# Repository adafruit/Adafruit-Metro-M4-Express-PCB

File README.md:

## Adafruit Metro M4 Express PCB

<a href="http://www.adafruit.com/products/3382"><br/>
Click here to purchase one from the Adafruit shop</a>

PCB files for the Adafruit Metro Express M4. PCB format is EagleCAD schematic and board layout

For more details, check out the product pages at
* https://www.adafruit.com/products/3382

### Description

Are you ready? Really ready? Cause here comes the fastest, most powerful Metro ever. The Adafruit Metro M4 featuring the Microchip ATSAMD51. This Metro is like a bullet train, with it's 120MHz Cortex M4 with floating point support. Your code will zig and zag and zoom, and with a bunch of extra peripherals for support, this will for sure be your favorite new chipset.

To start off our ATSAMD51 journey we decided to kick it off with the classic 'Arduino compatible' shape and pinout you know and love. This Metro is the same size as the others, and is compatible with all our shields. It's got analog pins where you expect, and SPI/UART/I2C hardware support in the same spot as the Metro 328 and M0. But! It's powered with an ATSAMD51J19.

### License

Adafruit invests time and resources providing this open source design, please support Adafruit and open-source hardware by purchasing products from [Adafruit](https://www.adafruit.com)!

Designed by Limor Fried/Ladyada for Adafruit Industries.

Creative Commons Attribution/Share-Alike, all text above must be included in any redistribution. See license.txt for additional details.

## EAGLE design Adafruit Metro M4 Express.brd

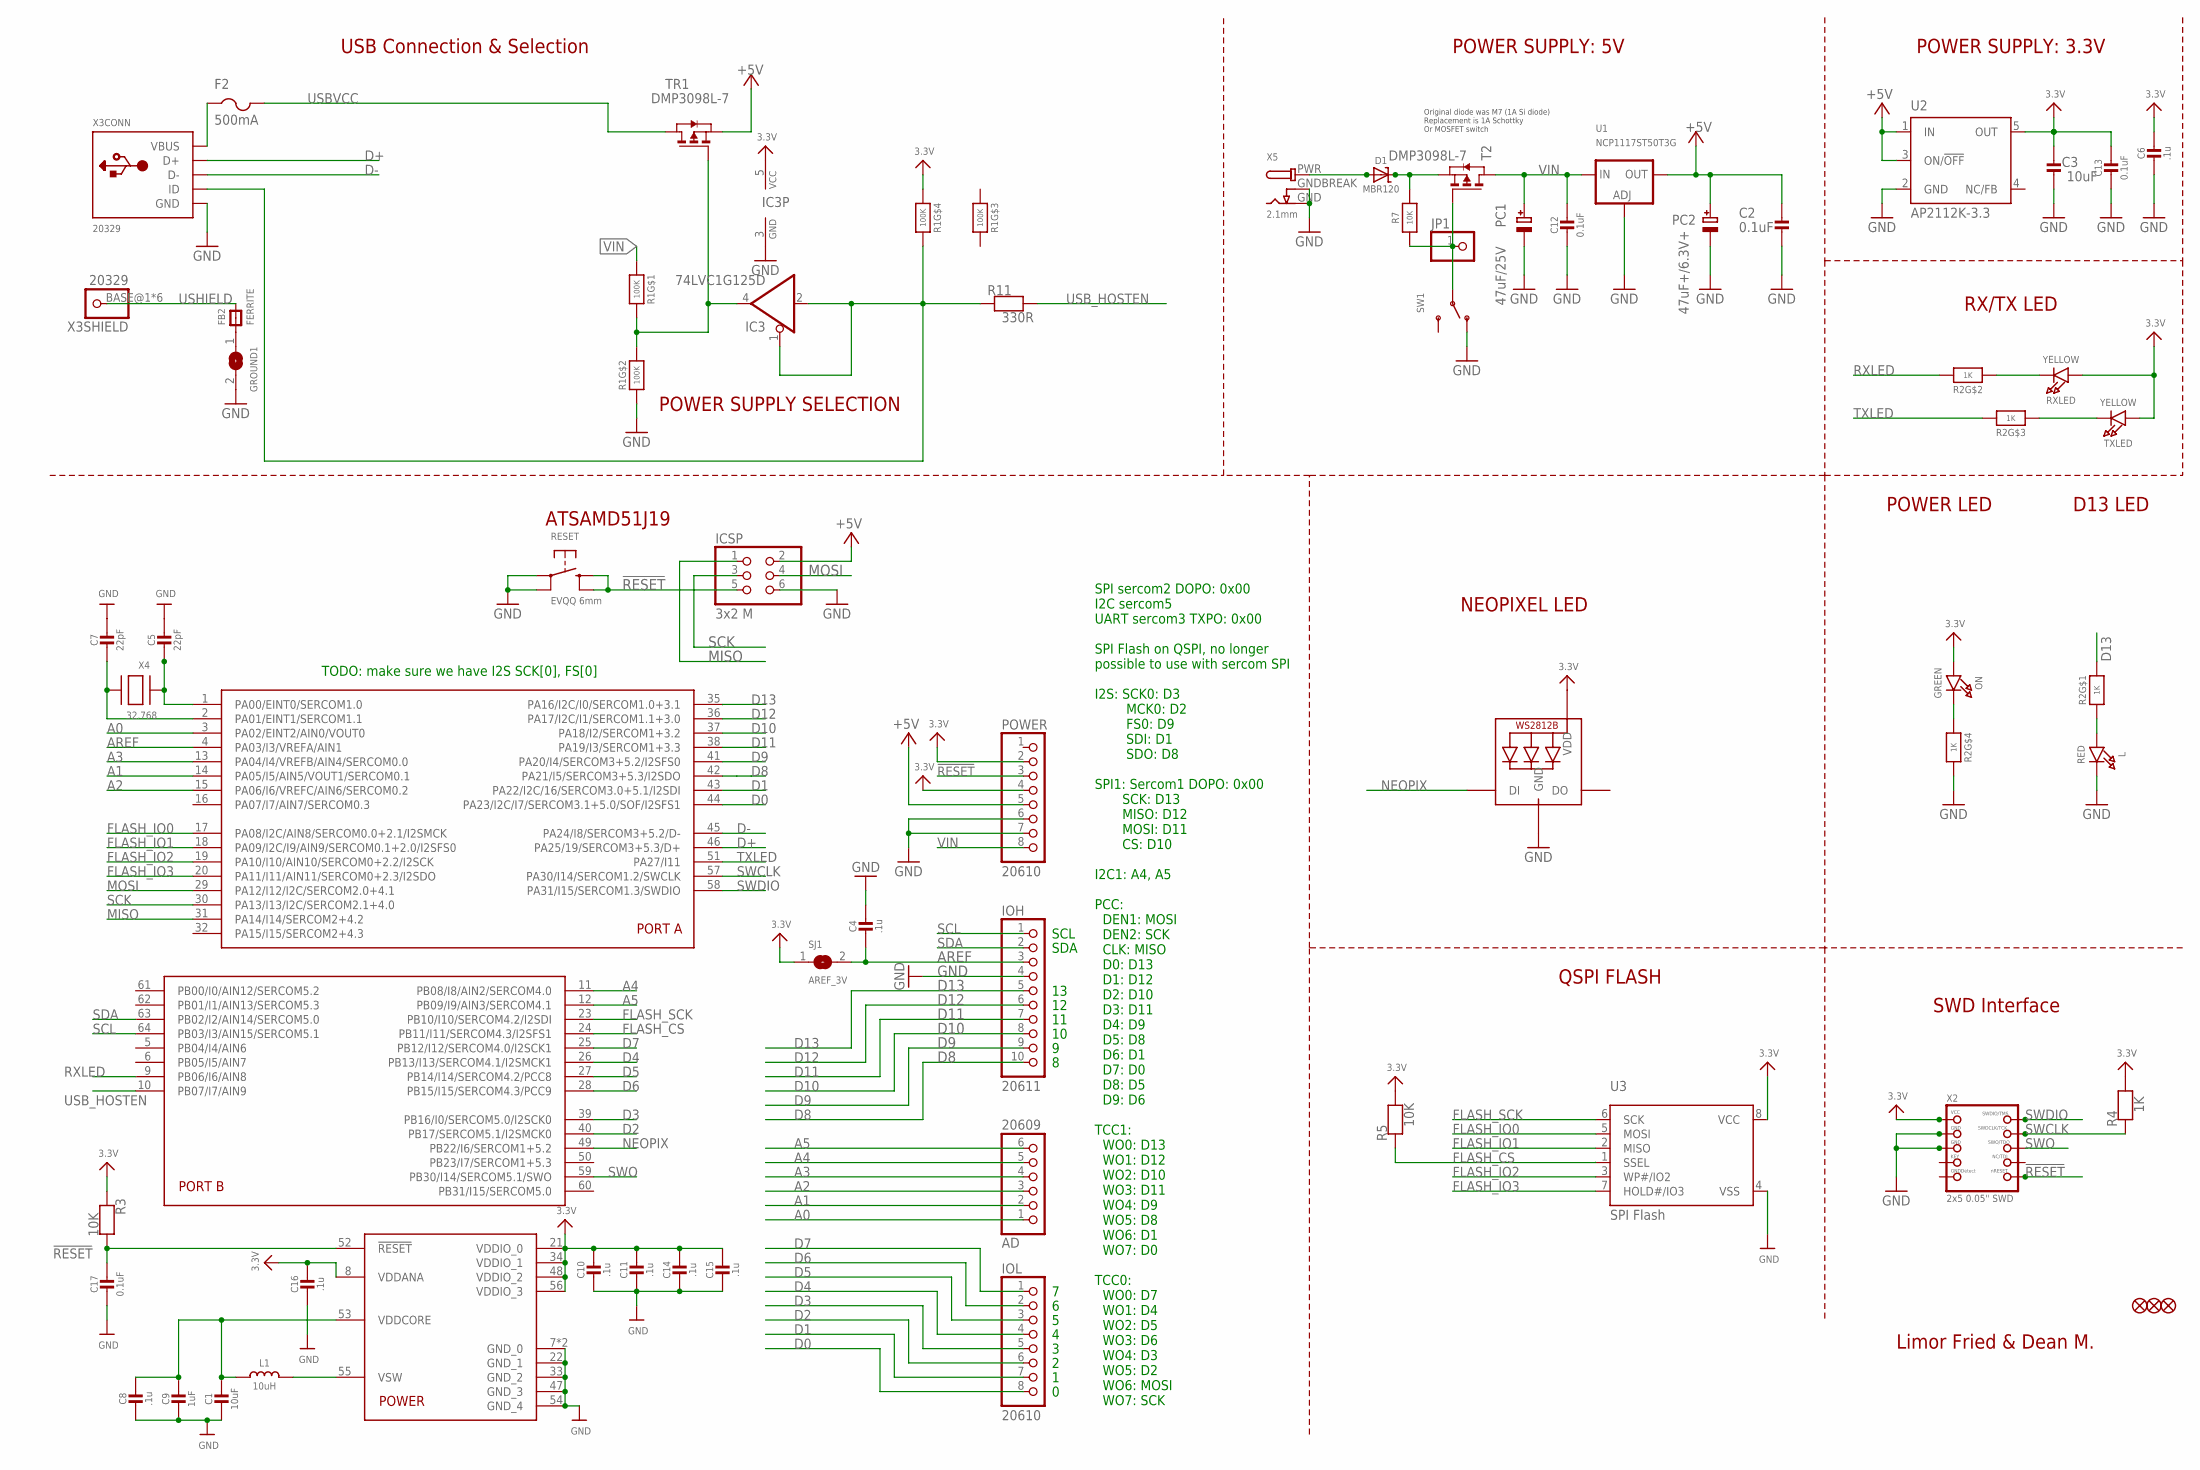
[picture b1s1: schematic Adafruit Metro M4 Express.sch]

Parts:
AD: 20609; 1X06_OVALWAVE
C1, C3: 10uF; 0805-NO
C2: 0.1uF; 0805-NO
C4, C6, C8, C10, C11, C14, C15, C16: .1u; 0603-NO
C5, C7: 22pF; 0603-NO
C9: 1uF; 0603-NO
C12, C13, C17: 0.1uF; 0603-NO
D1: MBR120; SOD-123
F2: 500mA; R1206
FB2: FERRITE; 0805-NO
FD1, FD2, FD3: FIDUCIAL_1MM
GROUND1: SOLDERJUMPERCLOSED; SOLDERJUMPER_CLOSEDWIRE
IC3: 74LVC1G125D; SOT23-5
ICSP: 3x2 M; 2X03_ROUND_70MIL
IOH: 20611; 1X10_OVALWAVE
IOL: 20610; 1X08_OVALWAVE
JP1: HEADER-1X1ROUND; 1X01_ROUND
L: RED; CHIPLED_0805_NOOUTLINE
L1: 10uH; INDUCTOR_1007
LED1: WS2812B3535; LED3535
ON: GREEN; CHIPLED_0805_NOOUTLINE
PC1: 47uF/25V; PANASONIC_D
PC2: 47uF+/6.3V+; PANASONIC_D
POWER: 20610; 1X08_OVALWAVE
R1: 100K; RESPACK_4X0603
R2: 1K; RESPACK_4X0603
R3, R5, R7: 10K; 0603-NO
R4: 1K; 0603-NO
R11: 330R; 0603-NO
RESET: EVQQ 6mm; EVQ-Q2
RXLED: YELLOW; CHIPLED_0805_NOOUTLINE
SJ1: AREF_3V; SOLDERJUMPER_CLOSEDWIRE
SW1: SWITCH_SPDT; SPDT_SMT_SSSS811101
T2: DMP3098L-7; SOT-23
TR1: DMP3098L-7; SOT-23
TXLED: YELLOW; CHIPLED_0805_NOOUTLINE
U1: NCP1117ST50T3G; SOT223-R
U2: AP2112K-3.3; SOT23-DBV
U3: SPI Flash; SOIC8_208MIL
U$1: ATSAMD51J; PQFN64-1
X2: 2x5 0.05" SWD; 2X05_1.27MM_BOX_POSTS
X3: 20329; 4UCONN_20329_V2
X4: 32.768; XTAL3215
X5: 2.1mm; DCJACK_2MM_PTH

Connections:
3.3V: C3.2, C6.2, C10.2, C11.2, C13.1, C14.2, C15.2, C16.2, IC3.5 (VCC), LED1.2 (VDD), ON.A, POWER.2, POWER.4, R1.4 (1), R3.1, R4.2, R5.2, RXLED.A, SJ1.1, TXLED.A, U2.5 (OUT), U3.8 (VCC), U$1.8 (VDDANA), U$1.21 (VDDIO_0), U$1.34 (VDDIO_1), U$1.48 (VDDIO_2), U$1.56 (VDDIO_3), X2.1 (VCC)
!RESET: C17.2, ICSP.5, POWER.3, R3.2, RESET.B (S), RESET.B' (S1), U$1.52 (!RESET), X2.10 (NRESET)
+5V: C2.2, ICSP.2, PC2.+, POWER.5, TR1.2 (S), U1.2 (OUT), U1.4 (OUT), U2.1 (IN), U2.3 (ON/!OFF)
A0: AD.1, U$1.3 (PA02/EINT2/AIN0/VOUT0)
A1: AD.2, U$1.14 (PA05/I5/AIN5/VOUT1/SERCOM0.1)
A2: AD.3, U$1.15 (PA06/I6/VREFC/AIN6/SERCOM0.2)
A3: AD.4, U$1.13 (PA04/I4/VREFB/AIN4/SERCOM0.0)
A4: AD.5, U$1.11 (PB08/I8/AIN2/SERCOM4.0)
A5: AD.6, U$1.12 (PB09/I9/AIN3/SERCOM4.1)
AREF: C4.1, IOH.3, SJ1.2, U$1.4 (PA03/I3/VREFA/AIN1)
D0: IOL.8, U$1.44 (PA23/I2C/I7/SERCOM3.1+5.0/SOF/I2SFS1)
D1: IOL.7, U$1.43 (PA22/I2C/16/SERCOM3.0+5.1/I2SDI)
D2: IOL.6, U$1.40 (PB17/SERCOM5.1/I2SMCK0)
D3: IOL.5, U$1.39 (PB16/I0/SERCOM5.0/I2SCK0)
D4: IOL.4, U$1.26 (PB13/I13/SERCOM4.1/I2SMCK1)
D5: IOL.3, U$1.27 (PB14/I14/SERCOM4.2/PCC8)
D6: IOL.2, U$1.28 (PB15/I15/SERCOM4.3/PCC9)
D7: IOL.1, U$1.25 (PB12/I12/SERCOM4.0/I2SCK1)
D8: IOH.10, U$1.42 (PA21/I5/SERCOM3+5.3/I2SDO)
D9: IOH.9, U$1.41 (PA20/I4/SERCOM3+5.2/I2SFS0)
D10: IOH.8, U$1.37 (PA18/I2/SERCOM1+3.2)
D11: IOH.7, U$1.38 (PA19/I3/SERCOM1+3.3)
D12: IOH.6, U$1.36 (PA17/I2C/I1/SERCOM1.1+3.0)
D13: IOH.5, R2.8 (2), U$1.35 (PA16/I2C/I0/SERCOM1.0+3.1)
D+: U$1.46 (PA25/19/SERCOM3+5.3/D+), X3.D+
D-: U$1.45 (PA24/I8/SERCOM3+5.2/D-), X3.D-
FLASH_CS: R5.1, U3.1 (SSEL), U$1.24 (PB11/I11/SERCOM4.3/I2SFS1)
FLASH_IO0: U3.5 (MOSI), U$1.17 (PA08/I2C/AIN8/SERCOM0.0+2.1/I2SMCK)
FLASH_IO1: U3.2 (MISO), U$1.18 (PA09/I2C/I9/AIN9/SERCOM0.1+2.0/I2SFS0)
FLASH_IO2: U3.3 (WP#/IO2), U$1.19 (PA10/I10/AIN10/SERCOM0+2.2/I2SCK)
FLASH_IO3: U3.7 (HOLD#/IO3), U$1.20 (PA11/I11/AIN11/SERCOM0+2.3/I2SDO)
FLASH_SCK: U3.6 (SCK), U$1.23 (PB10/I10/SERCOM4.2/I2SDI)
GND: C1.2, C2.1, C3.1, C4.2, C5.2, C6.1, C7.2, C8.1, C9.2, C10.1, C11.1, C12.2, C13.2, C14.1, C15.1, C16.1, C17.1, GROUND1.2, IC3.3 (GND), ICSP.6, IOH.4, L.C, LED1.4 (GND), PC1.-, PC2.-, POWER.6, POWER.7, R1.2 (1), R2.5 (2), RESET.A, RESET.A' (P1), SW1.A (O), U1.1 (ADJ), U2.2 (GND), U3.4 (VSS), U$1.7 (GND_0), U$1.22 (GND_1), U$1.33 (GND_2), U$1.47 (GND_3), U$1.54 (GND_4), U$1.EXP (GND_0), X2.3 (GND), X2.5 (GND), X3.GND, X5.GND, X5.GNDBREAK
MISO: ICSP.1, U$1.31 (PA14/I14/SERCOM2+4.2)
MOSI: ICSP.4, U$1.29 (PA12/I12/I2C/SERCOM2.0+4.1)
unnamed: L.A, R2.1
unnamed: FB2.1, GROUND1.1
unnamed: ON.C, R2.4 (1)
unnamed: L1.P$2 (2), U$1.55 (VSW)
unnamed: R2.2 (1), RXLED.C
unnamed: R2.3 (1), TXLED.C
unnamed: C5.1, U$1.1 (PA00/EINT0/SERCOM1.0), X4.P$1
unnamed: IC3.1 (OE), IC3.2 (I), R1.5 (2), R11.1, X3.ID
unnamed: IC3.4 (O), R1.7 (2), R1.8 (2), TR1.3 (G)
unnamed: C7.1, U$1.2 (PA01/EINT1/SERCOM1.1), X4.P$2
unnamed: D1.C, R7.2, T2.2 (S)
NEOPIX: LED1.1 (DI), U$1.49 (PB22/I6/SERCOM1+5.2)
PWRIN: D1.A, X5.PWR
PWR_SWITCH: JP1.1, R7.1, SW1.B, T2.3 (G)
RXLED: R2.7 (2), U$1.9 (PB06/I6/AIN8)
SCK: ICSP.3, U$1.30 (PA13/I13/I2C/SERCOM2.1+4.0)
SCL: IOH.1, U$1.64 (PB03/I3/AIN15/SERCOM5.1)
SDA: IOH.2, U$1.63 (PB02/I2/AIN14/SERCOM5.0)
SWCLK: R4.1, U$1.57 (PA30/I14/SERCOM1.2/SWCLK), X2.4 (SWDCLK)
SWDIO: U$1.58 (PA31/I15/SERCOM1.3/SWDIO), X2.2 (SWDIO)
SWO: U$1.59 (PB30/I14/SERCOM5.1/SWO), X2.6 (SWO)
TXLED: R2.6 (2), U$1.51 (PA27/I11)
USBVCC: F2.2, TR1.1 (D)
USB_HOSTEN: R11.2, U$1.10 (PB07/I7/AIN9)
USHIELD: FB2.2, X3.BASE@1 (1), X3.BASE@2 (1), X3.SPRT@1 (1), X3.SPRT@2 (1), X3.SPRT@3 (1), X3.SPRT@4 (1)
VBUS: F2.1, X3.VBUS
VDDCORE: C1.1, C8.2, C9.1, L1.P$1 (1), U$1.53 (VDDCORE)
VIN: C12.1, PC1.+, POWER.8, R1.1, T2.1 (D), U1.3 (IN)

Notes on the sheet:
SDA
SCL
Limor Fried & Dean M.
Original diode was M7 (1A Si diode) Replacement is 1A Schottky Or MOSFET switch
POWER SUPPLY: 5V
USB Connection & Selection
POWER SUPPLY: 3.3V
POWER LED
ATSAMD51J19
POWER SUPPLY SELECTION
D13 LED
RX/TX LED
NEOPIXEL LED
QSPI FLASH
SWD Interface
SPI sercom2 DOPO: 0x00 I2C sercom5 UART sercom3 TXPO: 0x00 SPI Flash on QSPI, no longer possible to use with sercom SPI I2S: SCK0: D3 MCK0: D2 FS0: D9 SDI: D1 SDO: D8 SPI1: Sercom1 DOPO: 0x00 SCK: D13 MISO: D12 MOSI: D11 CS: D10 I2C1: A4, A5 PCC: DEN1: MOSI DEN2: SCK CLK: MISO D0: D13 D1: D12 D2: D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
TODO: make sure we have I2S SCK[0], FS[0]

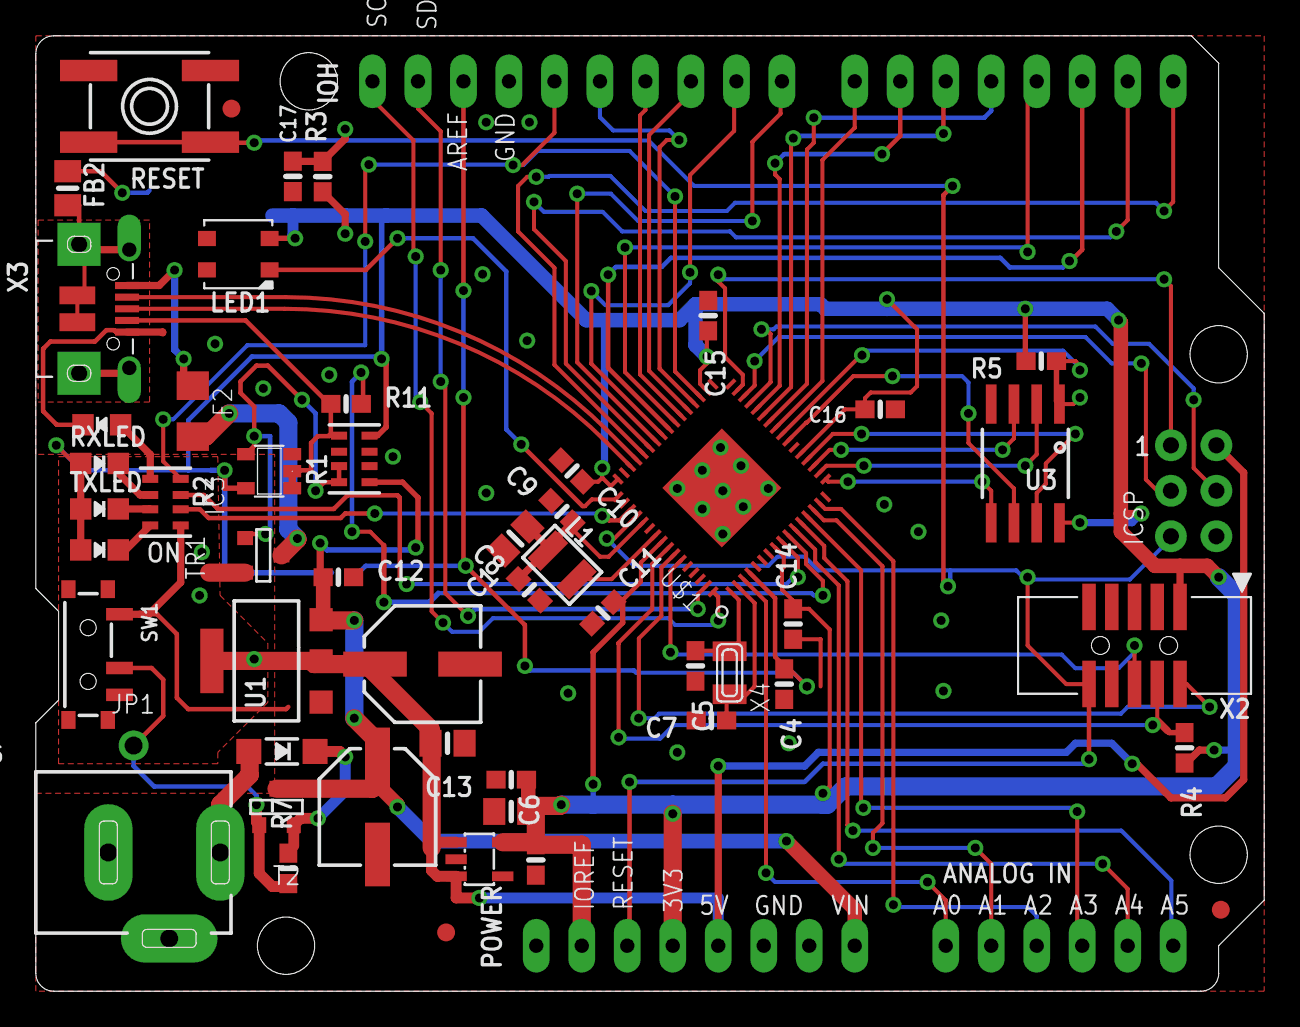
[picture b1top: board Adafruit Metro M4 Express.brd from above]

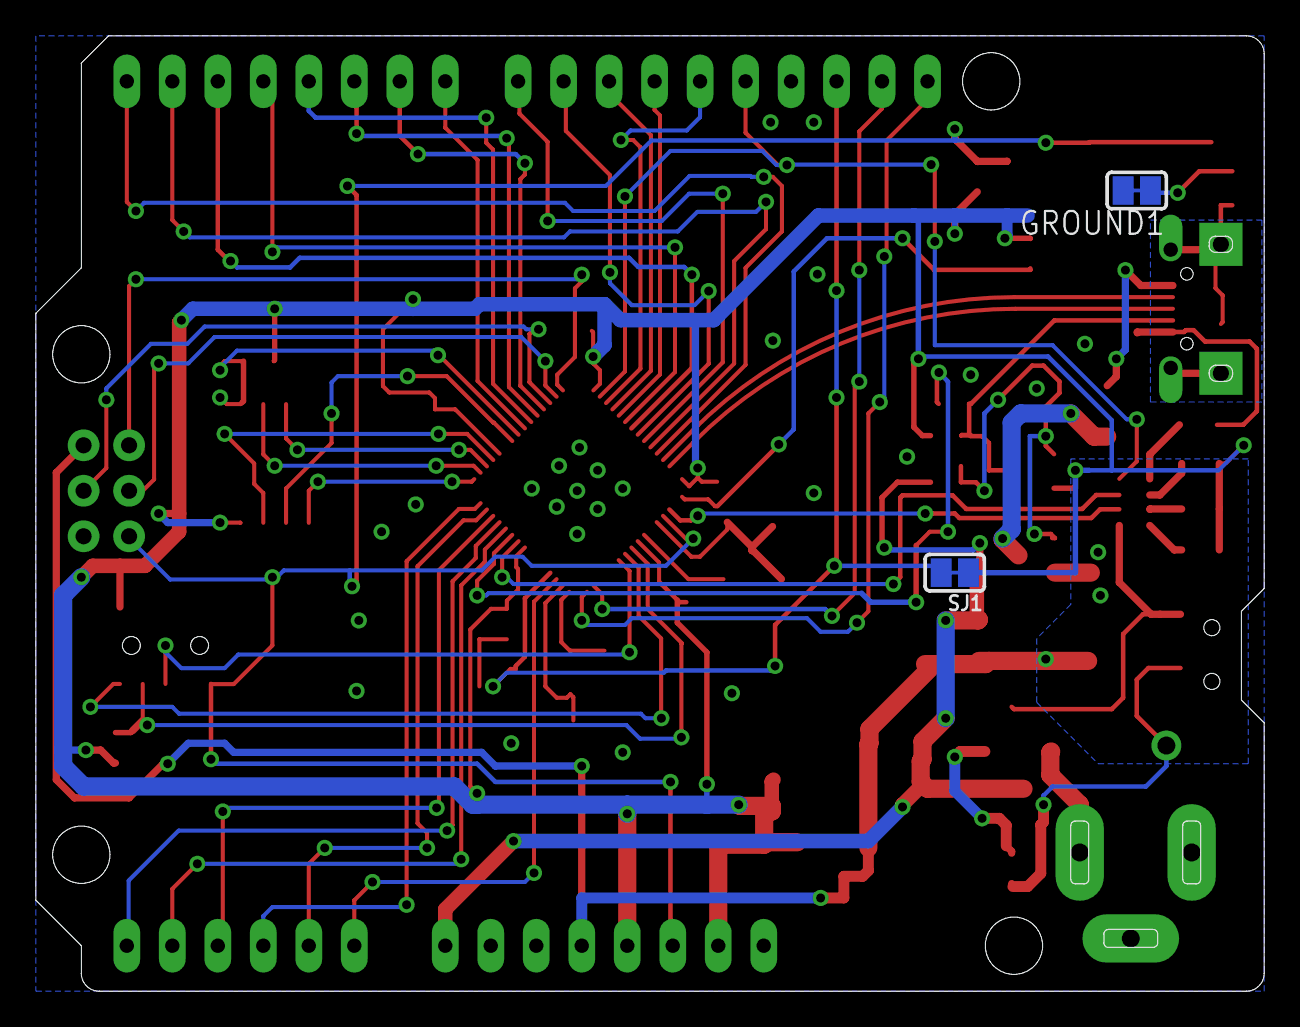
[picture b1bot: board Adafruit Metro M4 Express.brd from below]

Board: 2 copper layers, 68.6 x 53.3 mm, 61 parts (3 on the bottom side), 63 nets.

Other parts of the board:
U$23: METROM4_REVF_TOP
U$27: METROM4_REVF_BOT

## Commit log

2018-06-17 init
2022-04-27 Added PrettyPins

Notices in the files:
parts and their libraries:
microbuilder: This work is placed in the public domain, and may be freely used for commercial and non-commercial work with the following conditions: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
